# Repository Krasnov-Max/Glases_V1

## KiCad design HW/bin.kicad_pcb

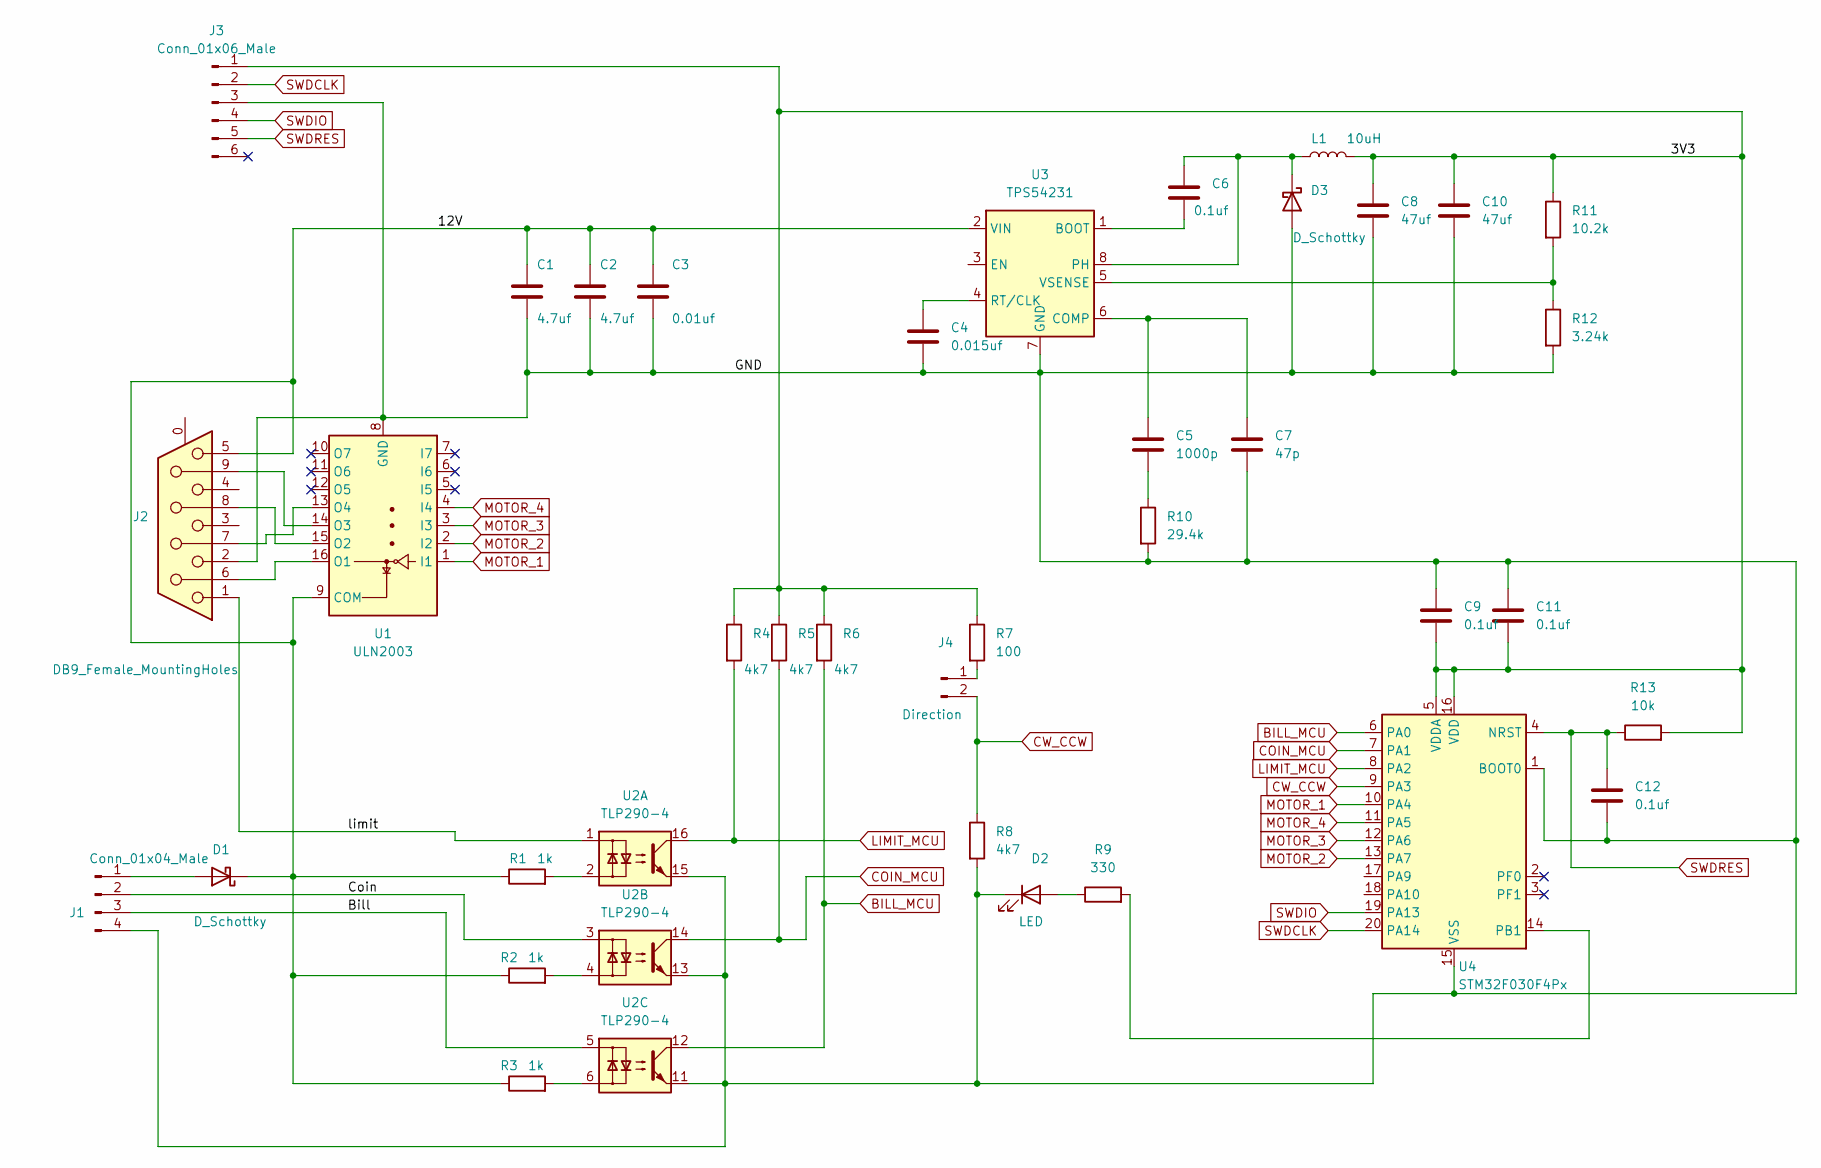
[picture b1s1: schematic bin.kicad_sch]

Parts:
C1, C2: 4.7uf; C_1206_3216Metric
C3: 0.01uf; C_1206_3216Metric
C4: 0.015uf; R_0603_1608Metric
C5: 1000p; R_0603_1608Metric
C6, C9, C11, C12: 0.1uf; R_0603_1608Metric
C7: 47p; R_0603_1608Metric
C8, C10: 47uf; R_0603_1608Metric
D1, D3: D_Schottky; D_SMB_Handsoldering
D2: LED; R_0603_1608Metric
J1: Conn_01x04_Male; PinHeader_1x04_P2.54mm_Vertical
J2: DB9_Female_MountingHoles; DSUB-9_Female_Horizontal_P2.77x2.84mm_EdgePinOffset14.56mm_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
J3: Conn_01x06_Male; PinHeader_1x06_P2.54mm_Vertical
J4: Direction; PinHeader_1x02_P2.54mm_Vertical
L1: 10uH; L_Bourns-SRU8028_8.0x8.0mm
R1, R2, R3: 1k; R_0603_1608Metric
R4, R5, R6, R8: 4k7; R_0603_1608Metric
R7: 100; R_0603_1608Metric
R9: 330; R_0603_1608Metric
R10: 29.4k; R_0603_1608Metric
R11: 10.2k; R_0603_1608Metric
R12: 3.24k; R_0603_1608Metric
R13: 10k; R_0603_1608Metric
U1: ULN2003; SOIC-16_3.9x9.9mm_P1.27mm
U2: TLP290-4; SOP-16_4.55x10.3mm_P1.27mm
U3: TPS54231; SOIC-8_3.9x4.9mm_P1.27mm
U4: STM32F030F4Px; TSSOP-20_4.4x6.5mm_P0.65mm

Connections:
/3V3: C8.1, C9.2, C10.1, C11.2, J3.1, L1.2, R4.1, R5.1, R6.1, R7.1, R11.1, R13.2, U4.5 (VDDA), U4.16 (VDD)
/12V: C1.1, C2.1, C3.1, D1.1 (K), J2.5, R1.1, R2.1, R3.1, U1.9 (COM), U3.2 (VIN)
/Bill: J1.3, U2.5
/Coin: J1.2, U2.3
/GND: C1.2, C2.2, C3.2, C4.2, C7.2, C8.2, C9.1, C10.2, C11.1, C12.2, D2.1 (K), D3.2 (A), J1.4, J2.2, J3.3, R8.2, R10.2, R12.2, U1.8 (GND), U2.11, U2.13, U2.15, U3.7 (GND), U3.9 (GND), U4.1 (BOOT0), U4.15 (VSS)
/limit: J2.1, U2.1
BILL_MCU: R6.2, U2.12, U4.6 (PA0)
COIN_MCU: R5.2, U2.14, U4.7 (PA1)
CW_CCW: J4.2, R8.1, U4.9 (PA3)
LIMIT_MCU: R4.2, U2.16, U4.8 (PA2)
MOTOR_1: U1.1 (I1), U4.10 (PA4)
MOTOR_2: U1.2 (I2), U4.13 (PA7)
MOTOR_3: U1.3 (I3), U4.12 (PA6)
MOTOR_4: U1.4 (I4), U4.11 (PA5)
unnamed: C4.1, U3.4 (RT/CLK)
unnamed: C5.1, C7.1, U3.6 (COMP)
unnamed: C5.2, R10.1
unnamed: C6.1, D3.1 (K), L1.1, U3.8 (PH)
unnamed: C6.2, U3.1 (BOOT)
unnamed: D1.2 (A), J1.1
unnamed: D2.2 (A), R9.1
unnamed: J2.6, U1.16 (O1)
unnamed: J2.7, U1.13 (O4)
unnamed: J2.8, U1.15 (O2)
unnamed: J2.9, U1.14 (O3)
unnamed: J4.1, R7.2
unnamed: R1.2, U2.2
unnamed: R2.2, U2.4
unnamed: R3.2, U2.6
unnamed: R9.2, U4.14 (PB1)
unnamed: R11.2, R12.1, U3.5 (VSENSE)
SWDCLK: J3.2, U4.20 (PA14)
SWDIO: J3.4, U4.19 (PA13)
SWDRES: C12.1, J3.5, R13.1, U4.4 (NRST)

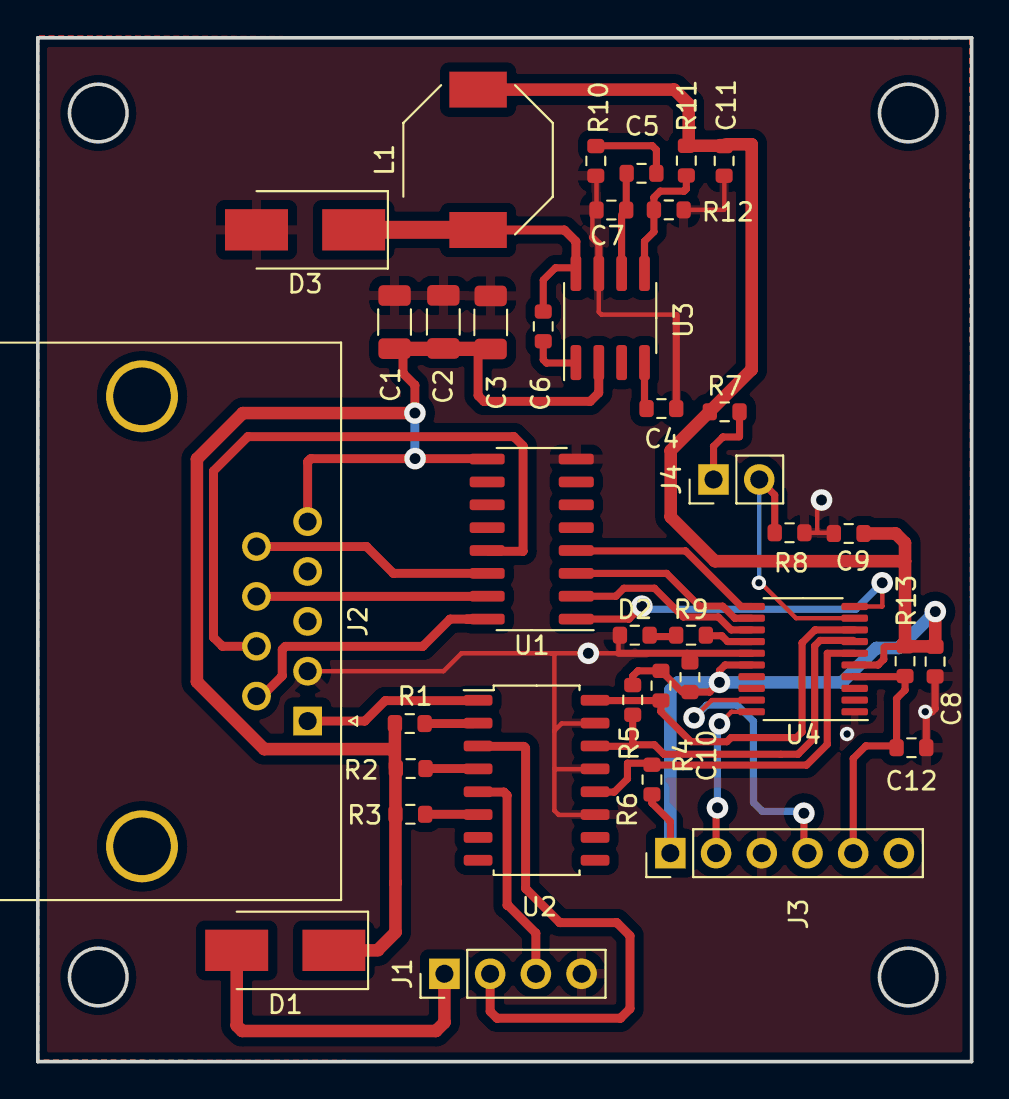
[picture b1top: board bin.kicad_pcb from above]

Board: 2 copper layers, 51.9 x 56.9 mm, 37 parts (0 on the bottom side), 34 nets.

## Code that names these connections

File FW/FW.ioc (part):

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Mcu.Name=STM32L031F(4-6)Px
Mcu.Package=TSSOP20
Mcu.UserName=STM32L031F4Px
PA0-CK_IN.GPIOParameters=GPIO_Label
PA0-CK_IN.GPIO_Label=BILL
PA0-CK_IN.Signal=GPXTI0
PA1.GPIOParameters=GPIO_Label
PA1.GPIO_Label=COIN
PA1.Signal=GPXTI1
PA13.Mode=Serial_Wire
PA13.Signal=SYS_SWDIO
PA14.Mode=Serial_Wire
PA14.Signal=SYS_SWCLK
PA2.GPIOParameters=GPIO_Label
PA2.GPIO_Label=LIMIT
PA2.Signal=GPXTI2
PA3.GPIOParameters=GPIO_Label
PA3.GPIO_Label=DIR
PA3.Signal=GPIO_Input
PA4.GPIOParameters=GPIO_Label
PA4.GPIO_Label=M1
PA4.Signal=GPIO_Output
PA5.GPIOParameters=GPIO_Label
PA5.GPIO_Label=M2
PA5.Signal=GPIO_Output
PA6.GPIOParameters=GPIO_Label
PA6.GPIO_Label=M3
PA6.Signal=GPIO_Output
PA7.GPIOParameters=GPIO_Label
PA7.GPIO_Label=M4
PA7.Signal=GPIO_Output
PB1.GPIOParameters=GPIO_Label
PB1.GPIO_Label=LED
PB1.Signal=GPIO_Output
RCC.HSE_VALUE=8000000
RCC.SYSCLKFreq_VALUE=32000000
RCC.SYSCLKSource=RCC_SYSCLKSOURCE_PLLCLK
board=custom

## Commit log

2022-05-25 First version, no modem, no BT
2022-06-09 Edir .gitignore file
